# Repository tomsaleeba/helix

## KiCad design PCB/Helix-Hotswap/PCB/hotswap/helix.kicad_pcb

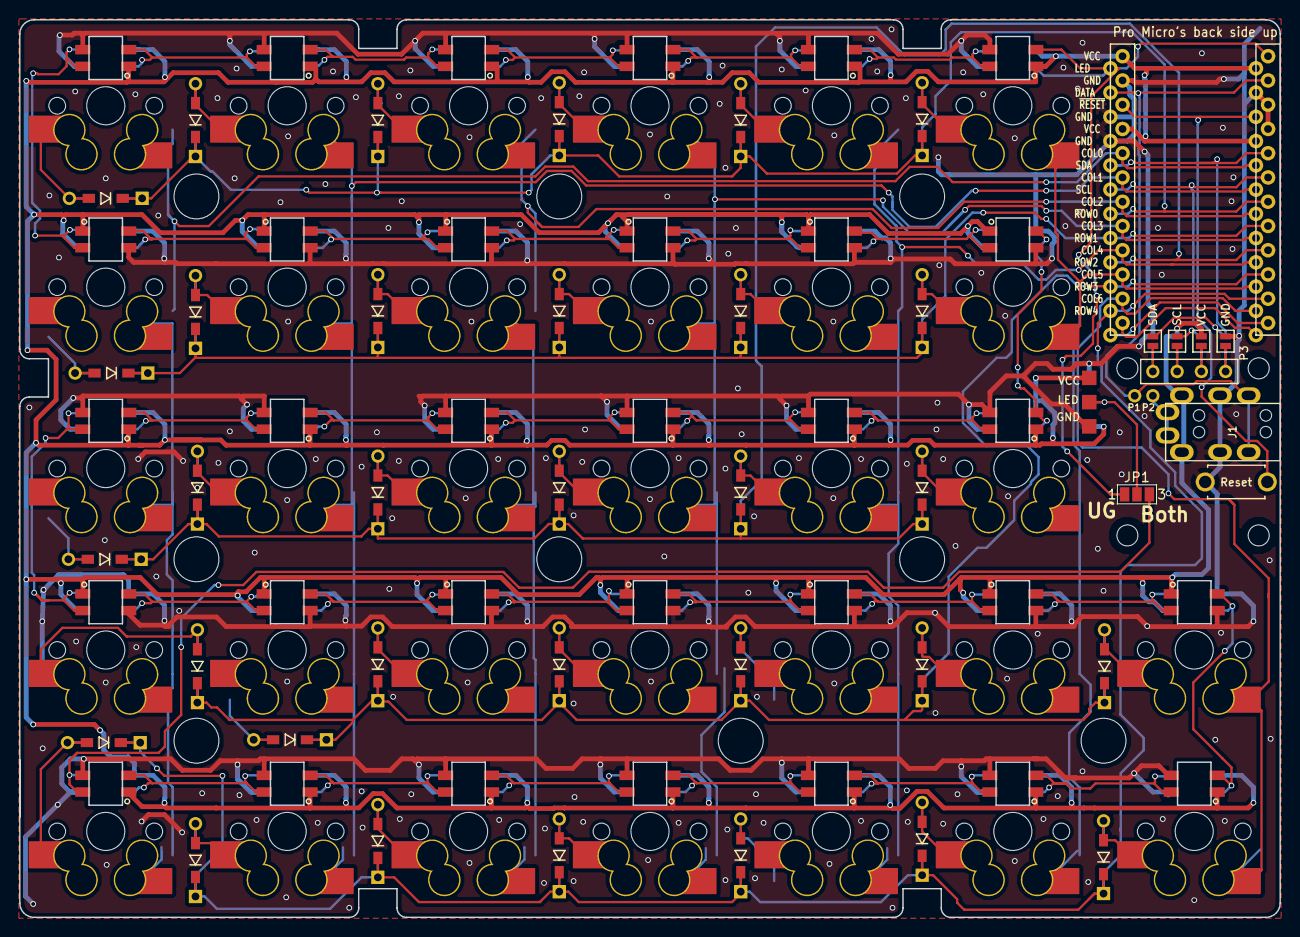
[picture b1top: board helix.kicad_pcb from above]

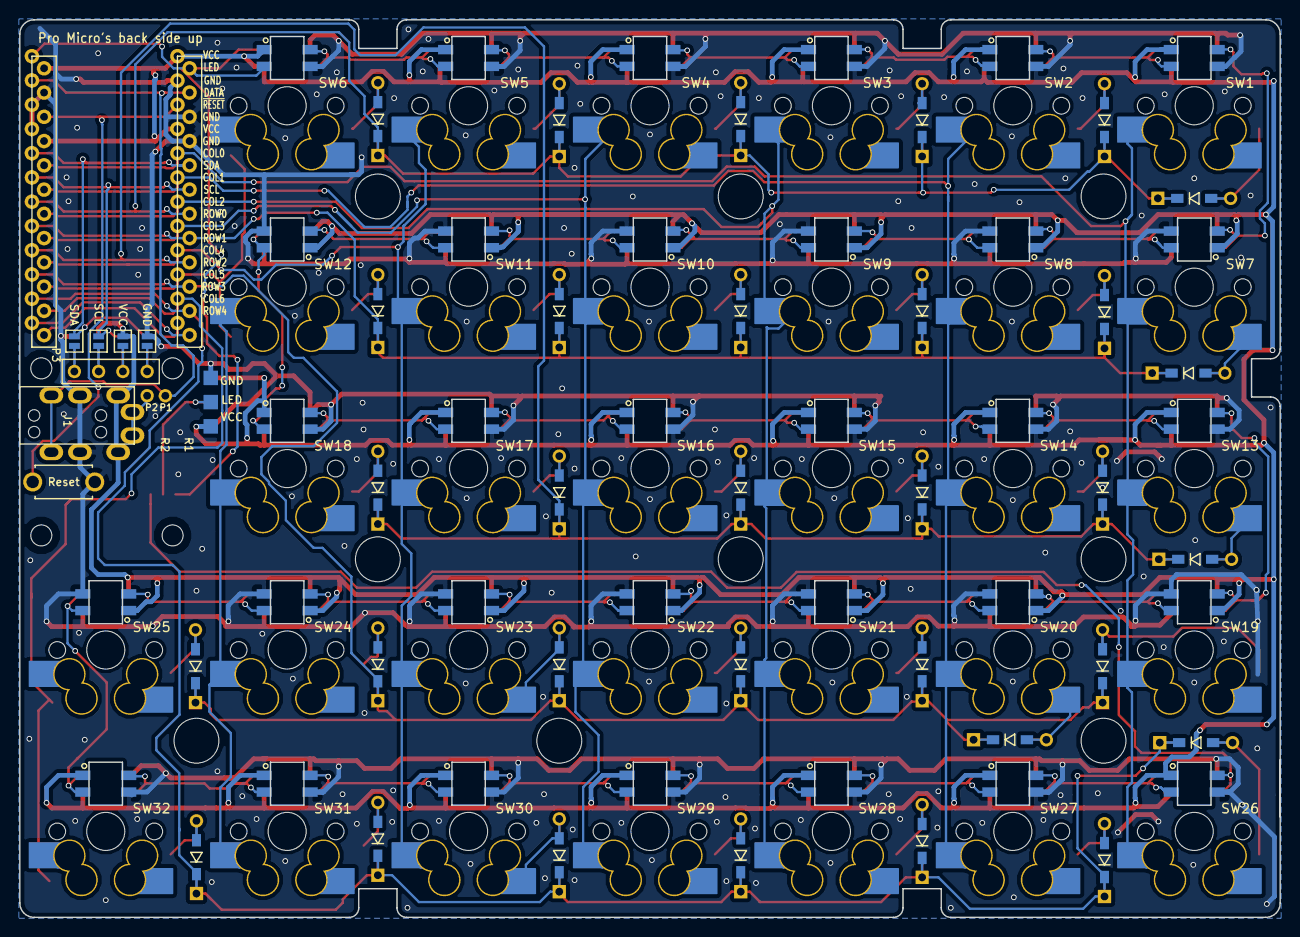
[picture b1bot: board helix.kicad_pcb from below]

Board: 2 copper layers, 132.0 x 94.0 mm, 126 parts (5 on the bottom side), 91 nets.

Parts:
D1, D2, D3, D4, D5, D6, D7, D8, D9, D10, D11, D12, D13, D14, D15, D16, D17, D18, D19, D20, D21, D22, D23, D24, D25, D26, D27, D28, D29, D30, D31, D32: D; D3_TH_SMD
H1, H2, H3, H4, H5, H6, H7, H8, H9: MountingHole; HOLE_M2_TH
H10, H11, H12, H13: MountingHole; HOLE_M2
J1: MJ-4PP-9; MJ-4PP-9_rev2
JP1: Jumper_NC_Dual; SolderJumper-3_P1.3mm_Open_Pad1.0x1.5mm_NumberLabels
JP4, JP11: GND; Jumper
JP5, JP10: VCC; Jumper
JP6, JP9: SCL; Jumper
JP7, JP8: SDA; Jumper
P1, P2: CONN_01X01; 1PIN_0.1
P3: OLED; MY_SIL-4
P4: LED; StripLED_rev
SW1, SW2, SW3, SW4, SW5, SW6, SW7, SW8, SW9, SW10, SW11, SW12, SW13, SW14, SW15, SW16, SW17, SW18, SW19, SW20, SW21, SW22, SW23, SW24, SW25, SW26, SW27, SW28, SW29, SW30, SW31, SW32: SW_PUSH; MXOnly-1U-Hotswap-Double-noled
SW33: Reset; SW_3.5x6.0_TH
U1, U1#2: ProMicro; ProMicro_rev
U2, U3, U4, U5, U6, U7, U8, U9, U10, U11, U12, U13, U14, U15, U16, U17, U18, U19, U20, U21, U22, U23, U24, U25, U26, U27, U28, U29, U30, U31, U32, U33: SK6812mini; SK6812MINI_rev

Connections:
/SCL: JP6.1, JP9.1, U1.6, U1#2.6
/SDA: JP7.1, JP8.1, U1.5, U1#2.5
/ex1: U1.12, U1#2.12
/ex2: U1.13, U1#2.13
/~RESET: SW33.2, U1.22, U1#2.22
GND: J1.C, JP4.1, JP11.1, P4.3, SW33.1, U1.3, U1.4, U1.23, U1#2.3, U1#2.4, U1#2.23, U2.2, U3.2, U4.2, U5.2, U6.2, U7.2, U8.2, U9.2, U10.2, U11.2, U12.2, U13.2, U14.2, U15.2, U16.2, U17.2, U18.2, U19.2, U20.2, U21.2, U22.2, U23.2, U24.2, U25.2, U26.2, U27.2, U28.2, U29.2, U30.2, U31.2, U32.2, U33.2
LED: JP1.1, U1.1, U1#2.1, U7.3
unnamed: D1.2, SW1.2
unnamed: D2.2, SW2.2
unnamed: D3.2, SW3.2
unnamed: D4.2, SW4.2
unnamed: D5.2, SW5.2
unnamed: D6.2, SW6.2
unnamed: D7.2, SW7.2
unnamed: D8.2, SW8.2
unnamed: D9.2, SW9.2
unnamed: D10.2, SW10.2
unnamed: D11.2, SW11.2
unnamed: D12.2, SW12.2
unnamed: D13.2, SW13.2
unnamed: D14.2, SW14.2
unnamed: D15.2, SW15.2
unnamed: D16.2, SW16.2
unnamed: D17.2, SW17.2
unnamed: D18.2, SW18.2
unnamed: D19.2, SW19.2
unnamed: D20.2, SW20.2
unnamed: D21.2, SW21.2
unnamed: D22.2, SW22.2
unnamed: D23.2, SW23.2
unnamed: D24.2, SW24.2
unnamed: D25.2, SW25.2
unnamed: D26.2, SW26.2
unnamed: D27.2, SW27.2
unnamed: D28.2, SW28.2
unnamed: D29.2, SW29.2
unnamed: D30.2, SW30.2
unnamed: D31.2, SW31.2
unnamed: D32.2, SW32.2
unnamed: J1.A, P2.1
unnamed: JP1.2, P4.2
unnamed: JP1.3, U27.1
unnamed: JP4.2, JP8.2, P3.1
unnamed: JP5.2, JP9.2, P3.2
unnamed: JP6.2, JP10.2, P3.3
unnamed: JP7.2, JP11.2, P3.4
unnamed: U2.1, U8.3
unnamed: U2.3, U3.1
unnamed: U3.3, U4.1
unnamed: U4.3, U5.1
unnamed: U5.3, U6.1
unnamed: U6.3, U7.1
unnamed: U8.1, U9.3
unnamed: U10.1, U11.3
unnamed: U9.1, U10.3
unnamed: U11.1, U12.3
unnamed: U12.1, U13.3
unnamed: U13.1, U19.3
unnamed: U14.1, U20.3
unnamed: U14.3, U15.1
unnamed: U15.3, U16.1
unnamed: U16.3, U17.1
unnamed: U17.3, U18.1
unnamed: U18.3, U19.1
unnamed: U20.1, U21.3
unnamed: U21.1, U22.3
unnamed: U22.1, U23.3
unnamed: U23.1, U24.3
unnamed: U24.1, U25.3
unnamed: U25.1, U26.3
unnamed: U26.1, U33.3
unnamed: U27.3, U28.1
unnamed: U28.3, U29.1
unnamed: U29.3, U30.1
unnamed: U30.3, U31.1
unnamed: U31.3, U32.1
unnamed: U32.3, U33.1
VCC: J1.D, JP5.1, JP10.1, P4.1, U1.21, U1.24, U1#2.21, U1#2.24, U2.4, U3.4, U4.4, U5.4, U6.4, U7.4, U8.4, U9.4, U10.4, U11.4, U12.4, U13.4, U14.4, U15.4, U16.4, U17.4, U18.4, U19.4, U20.4, U21.4, U22.4, U23.4, U24.4, U25.4, U26.4, U27.4, U28.4, U29.4, U30.4, U31.4, U32.4, U33.4
col0: SW1.1, SW7.1, SW13.1, SW19.1, SW26.1, U1.20, U1#2.20
col1: SW2.1, SW8.1, SW14.1, SW20.1, SW27.1, U1.19, U1#2.19
col2: SW3.1, SW9.1, SW15.1, SW21.1, SW28.1, U1.18, U1#2.18
col3: SW4.1, SW10.1, SW16.1, SW22.1, SW29.1, U1.17, U1#2.17
col4: SW5.1, SW11.1, SW17.1, SW23.1, SW30.1, U1.16, U1#2.16
col5: SW6.1, SW12.1, SW18.1, SW24.1, SW31.1, U1.15, U1#2.15
col6: SW25.1, SW32.1, U1.14, U1#2.14
data: J1.B, P1.1, U1.2, U1#2.2
row0: D1.1, D2.1, D3.1, D4.1, D5.1, D6.1, U1.7, U1#2.7
row1: D7.1, D8.1, D9.1, D10.1, D11.1, D12.1, U1.8, U1#2.8
row2: D13.1, D14.1, D15.1, D16.1, D17.1, D18.1, U1.9, U1#2.9
row3: D19.1, D20.1, D21.1, D22.1, D23.1, D24.1, D25.1, U1.10, U1#2.10
row4: D26.1, D27.1, D28.1, D29.1, D30.1, D31.1, D32.1, U1.11, U1#2.11

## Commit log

2019-05-19 Added Hotswap
    Added 5 row, cherry mx hotswap kicad files
2019-10-24 chore: add photo
2019-10-24 feat: remove un-needed switches and LEDs from schematic
